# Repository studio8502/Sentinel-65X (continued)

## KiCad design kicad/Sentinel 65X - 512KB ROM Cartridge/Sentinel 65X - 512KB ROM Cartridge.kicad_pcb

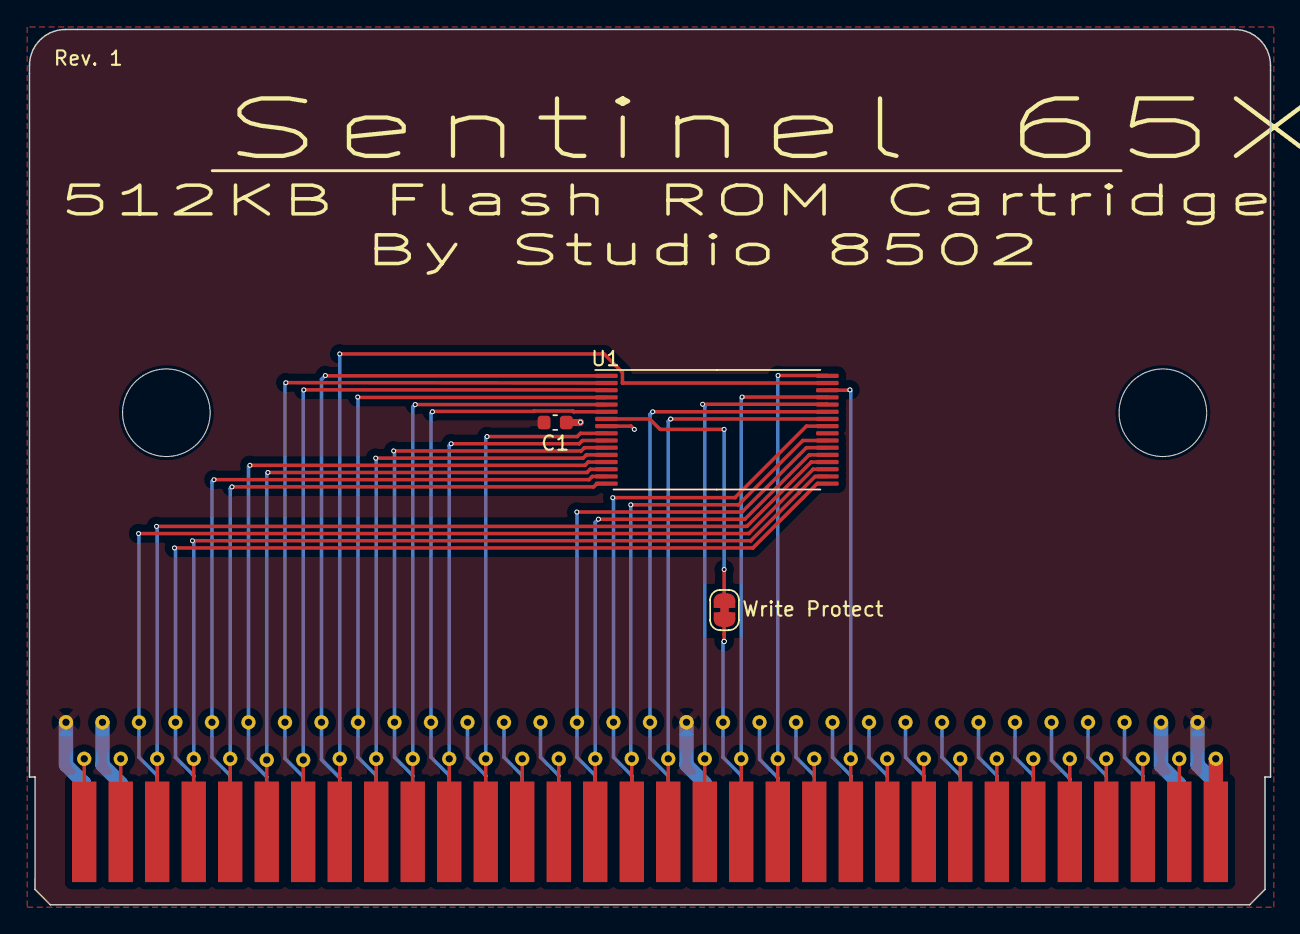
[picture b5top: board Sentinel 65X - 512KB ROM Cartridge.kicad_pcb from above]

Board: 2 copper layers, 86.4 x 60.9 mm, 4 parts (0 on the bottom side), 33 nets.

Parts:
C1: 100nF; C_0603_1608Metric
J1: 2x32 2.54mm Card Edge Connector; Conn_Edge_2x32_THT_2.54mm_Male
JP1: SolderJumper_2_Bridged; SolderJumper-2_P1.3mm_Bridged_RoundedPad1.0x1.5mm
U1: TSOP-I-32_14.4x8mm_P0.5mm

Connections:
+3.3V: C1.1, J1.a2, J1.a31, U1.8 (VDD)
/A0: J1.b30, U1.20 (A0)
/A1: J1.a30, U1.19 (A1)
/A2: J1.b29, U1.18 (A2)
/A3: J1.a29, U1.17 (A3)
/A4: J1.b28, U1.16 (A4)
/A5: J1.a28, U1.15 (A5)
/A6: J1.b27, U1.14 (A6)
/A7: J1.a27, U1.13 (A7)
/A8: J1.b26, U1.3 (A8)
/A9: J1.a26, U1.2 (A9)
/A10: J1.b25, U1.31 (A10)
/A11: J1.a25, U1.1 (A11)
/A12: J1.b24, U1.12 (A12)
/A13: J1.a24, U1.4 (A13)
/A14: J1.b23, U1.5 (A14)
/A15: J1.a23, U1.11 (A15)
/A16: J1.b22, U1.10 (A16)
/A17: J1.a22, U1.6 (A17)
/A18: J1.b21, U1.9 (A18)
/D0: J1.b18, U1.21 (D0)
/D1: J1.a18, U1.22 (D1)
/D2: J1.b17, U1.23 (D2)
/D3: J1.a17, U1.25 (D3)
/D4: J1.b16, U1.26 (D4)
/D5: J1.a16, U1.27 (D5)
/D6: J1.b15, U1.28 (D6)
/D7: J1.b14, U1.29 (D7)
/~CS6: J1.b11, U1.30 (~CE)
/~RD: J1.b13, U1.32 (~OE)
/~WR: J1.a14, JP1.1 (A)
GND: C1.2, J1.a1, J1.a15, J1.a32, U1.24 (GND)
unnamed: JP1.2 (B), U1.7 (~WE)

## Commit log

2023-12-06 Initial import of work in progress
2023-12-07 More work in progress
2023-12-14 Catchup to Rev0, V2
2023-12-14 Added PDF of schematic
2023-12-14 Added datasheets and manuals
2023-12-15 Pinouts updated
2023-12-16 Added audio mixing of cartridge audio
2023-12-16 logo import
2023-12-16 Updated schematic PDF
2023-12-16 Updated license terms
2023-12-17 Added programmable clock generator
2023-12-18 Switched glue logic to ATF1502 TQFP-44, added JTAG header
2023-12-18 Removed DV header, deferred to Rev1. Updated PDF schematic.
2023-12-18 Added project-specific library
2023-12-19 Added FPGA CDONE and reset pins to CPU GPIO. Added CDONE indicator LED.
2023-12-19 Added FPGA pins CDONE and RESET to the clock port.
2023-12-19 Adjusted VERA pinout for initial routing of Rev0 PCB
2023-12-19 Updated Rev0 schematic PDF
2023-12-19 Updated pinouts
2023-12-23 Updated schematic to add RTS/CTS flow control to debug UART (required by CPU's on-chip ROM monitor)
2024-02-07 Added version 3 and 4 prototype schematics
2024-03-07 Updated schematics and PCB files for prototype 4
2024-03-15 Updated prototype 4 V2 schematic
2024-03-17 Updated prototype 4V2 schematic
